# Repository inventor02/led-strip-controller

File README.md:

# led-strip-controller

The LED Strip Controller is a RP2040 (Pi Pico) based controller for a 12V DC LED strip we had lying around. Instead of
spending £20 on a cheap controller, why not spend much more (and countless hours) on making our own absurdly overengineered
one!?

## Firmware

The firmware, located in `firmware` is WIP.

## Hardware

### PCB

The entire controller is based around one PCB available in the `hardware/board` directory. It is designed using KiCad.

### Box

There is a box that can be 3D printed to fit the PCB and its components well. It is in the `hardware/box` directory, and
was designed using FreeCAD.

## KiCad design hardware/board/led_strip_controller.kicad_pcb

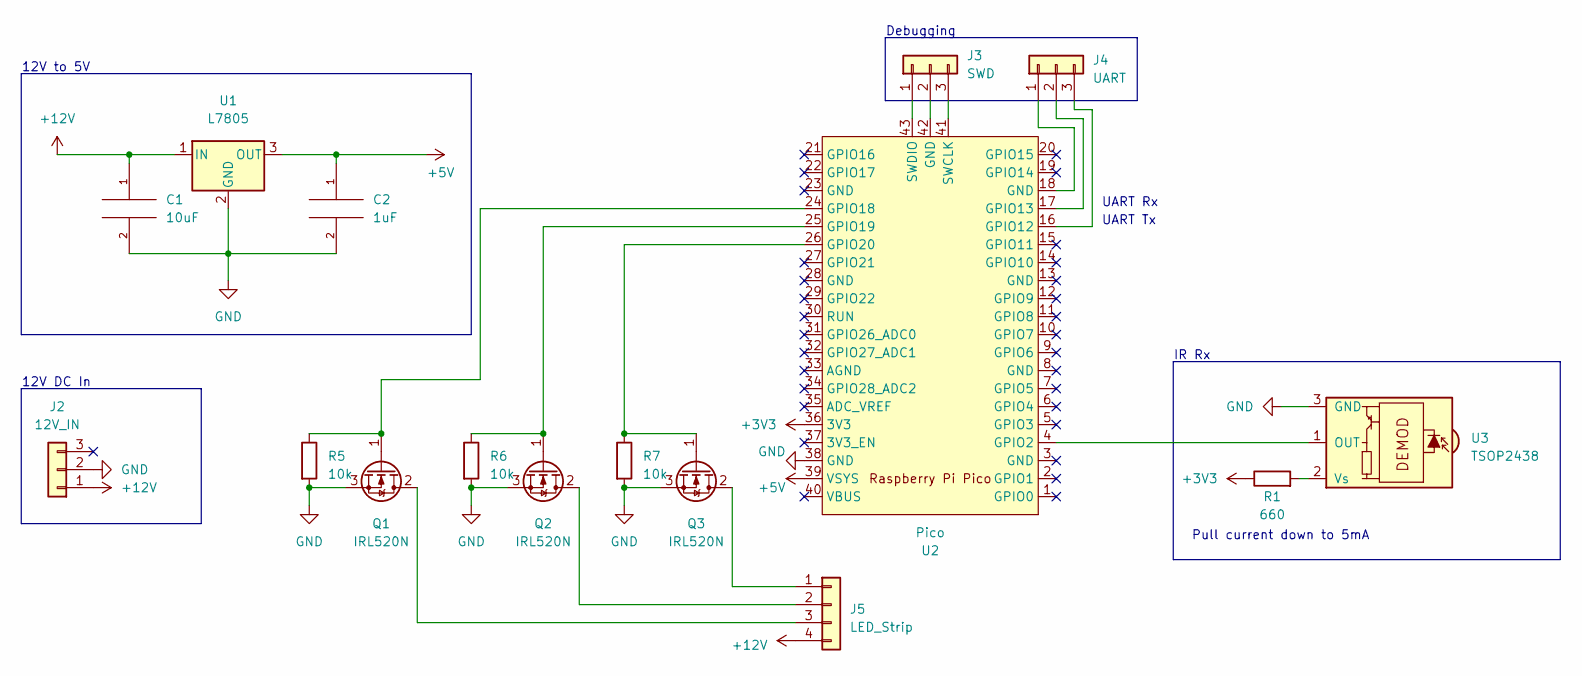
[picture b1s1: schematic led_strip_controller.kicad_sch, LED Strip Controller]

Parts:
C1: 10uF; CP_Radial_D4.0mm_P2.00mm
C2: 1uF; CP_Radial_D4.0mm_P2.00mm
J2: 12V_IN; BarrelJack_Wuerth_6941xx301002
J3: SWD; PinHeader_1x03_P2.00mm_Vertical
J4: UART; PinHeader_1x03_P2.00mm_Vertical
J5: LED_Strip; Molex_MicroClasp_55935-0410_1x04_P2.00mm_Horizontal
Q1, Q2, Q3: IRL520N; TO-220-3_Vertical
R1: 660; R_Axial_DIN0207_L6.3mm_D2.5mm_P7.62mm_Horizontal
R5, R6, R7: 10k; R_Axial_DIN0207_L6.3mm_D2.5mm_P7.62mm_Horizontal
U1: L7805; TO-220-3_Horizontal_TabUp
U2: Pico; RPi_Pico_SMD_TH
U3: TSOP2438; Vishay_MOLD-3Pin

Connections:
+3V3: R1.1, U2.36 (3V3)
+5V: C2.1, U1.3 (OUT), U2.39 (VSYS)
+12V: C1.1, J2.1, J5.4, U1.1 (IN)
GND: C1.2, C2.2, J2.2, Q1.3 (S), Q2.3 (S), Q3.3 (S), R5.2, R6.2, R7.2, U1.2 (GND), U2.38 (GND), U3.3 (GND)
unnamed: J3.1, U2.43 (SWDIO)
unnamed: J3.2, U2.42 (GND)
unnamed: J3.3, U2.41 (SWCLK)
unnamed: J4.1, U2.18 (GND)
unnamed: J4.2, U2.17 (GPIO13)
unnamed: J4.3, U2.16 (GPIO12)
unnamed: J5.1, Q3.2 (D)
unnamed: J5.2, Q2.2 (D)
unnamed: J5.3, Q1.2 (D)
unnamed: Q1.1 (G), R5.1, U2.24 (GPIO18)
unnamed: Q2.1 (G), R6.1, U2.25 (GPIO19)
unnamed: Q3.1 (G), R7.1, U2.26 (GPIO20)
unnamed: U2.4 (GPIO2), U3.1 (OUT)
unnamed: R1.2, U3.2 (Vs)

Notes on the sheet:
UART Rx
Pull current down to 5mA
Debugging
UART Tx
12V DC In
12V to 5V
IR Rx

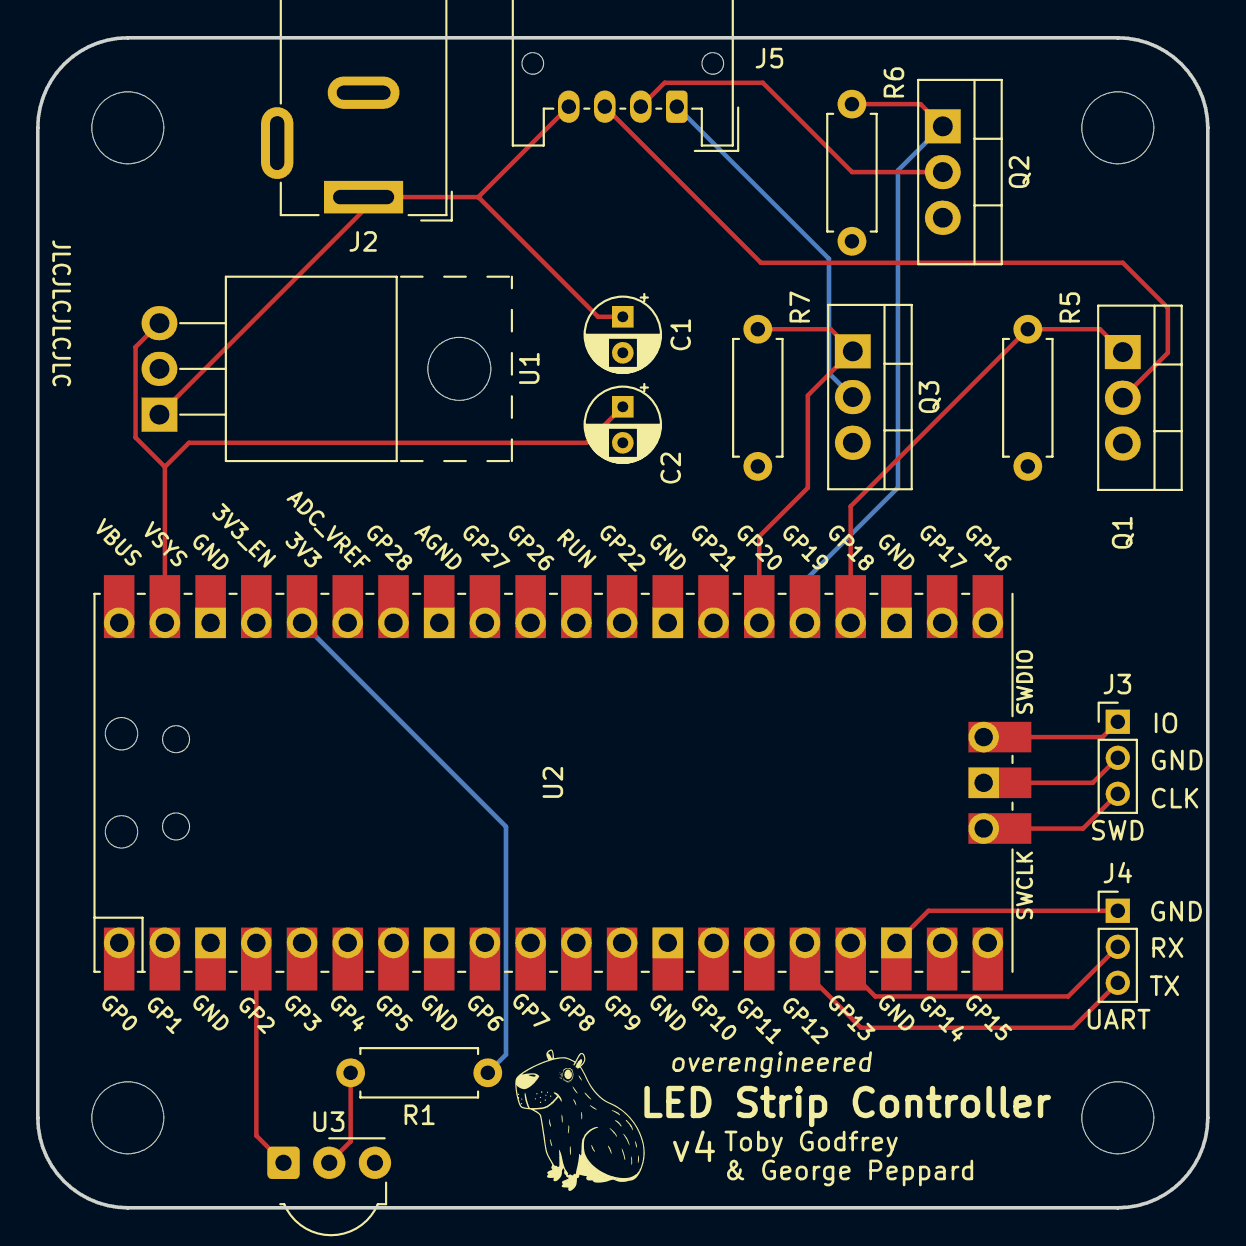
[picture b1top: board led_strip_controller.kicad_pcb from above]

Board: 2 copper layers, 65.0 x 65.0 mm, 16 parts (0 on the bottom side), 18 nets.

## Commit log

2023-03-03 vscode config
2023-03-03 fixed the version issue that was found in the cmake version specifier bit of the cmake lists
2023-03-03 setup
2023-03-03 configs
2023-03-11 feat: basic UART out and pin select
2023-03-12 ir files
2023-03-15 calculations and breakdown
2023-03-18 methods
2023-03-22 add pwm stuff
2023-03-22 reorg
2023-03-22 no volatile :(
2023-03-24 added clangd folder to gitignore
2023-06-06 updated submodule
2023-06-06 fixed delay
2023-06-06 timings
2023-06-06 ISR fixes
2023-06-06 printf
2023-06-06 add PIO
2023-06-14 chore: update pico SDK
2023-06-15 feat: rewrite PIO
